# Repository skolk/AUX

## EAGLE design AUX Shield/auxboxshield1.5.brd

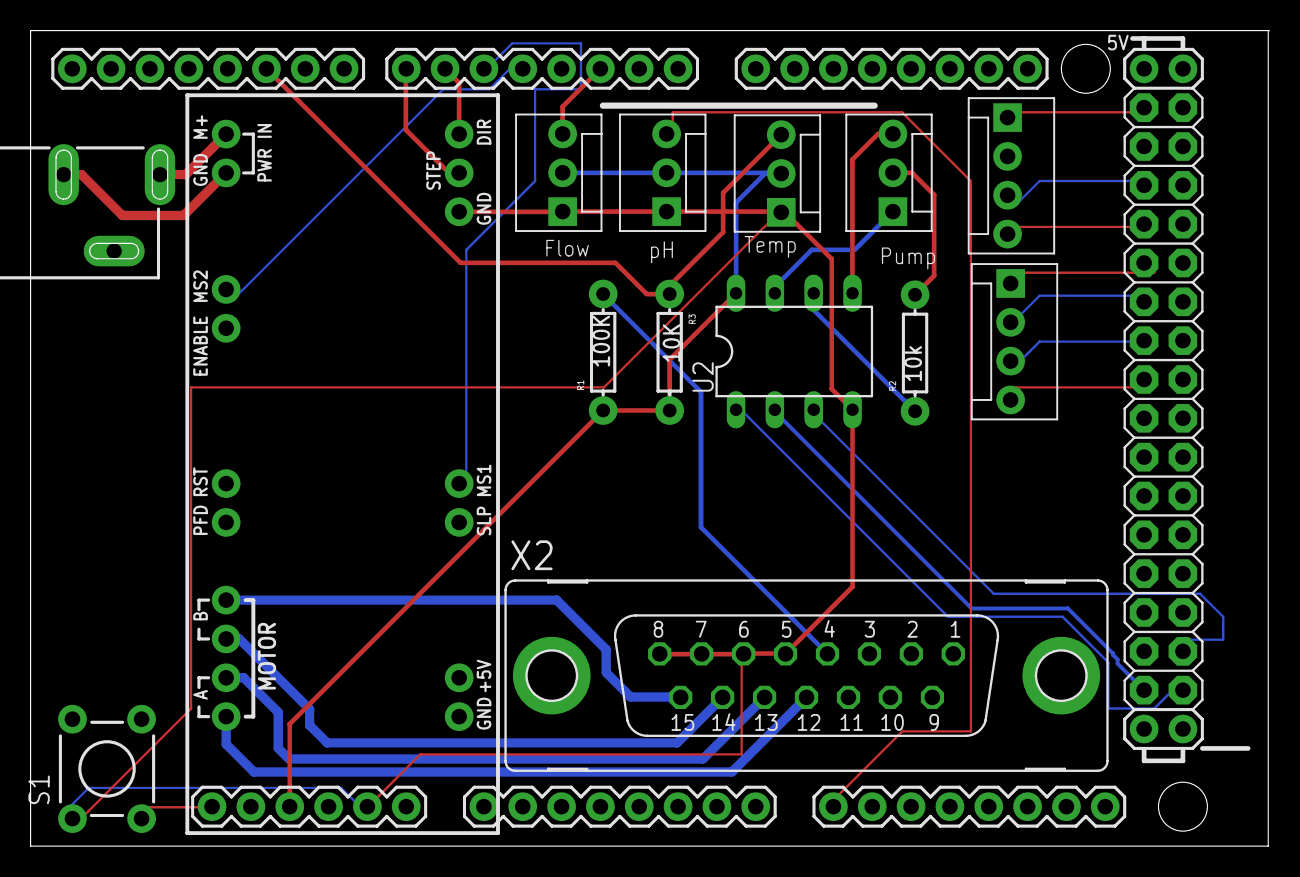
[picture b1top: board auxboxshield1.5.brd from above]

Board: 2 copper layers, 81.0 x 53.3 mm, 15 parts (0 on the bottom side), 34 nets.

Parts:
AMSHD1: ARDUINO_MEGA_SHIELD
EASYDRIVER_V44: EASYDRIVER_V44
JP1, JP2, JP3, JP11: MOLEX-1X3
JP4, JP5: MOLEX-1X4
R1: 100K; AXIAL-0.3
R2: 10k; AXIAL-0.3
R3: 10K; AXIAL-0.3
S1: SWITCH-MOMENTARY-2PTH_EZ; TACTILE-PTH-EZ
U2: MCP41XXXDIL; DIL-08
X1: SCD-014-A
X2: F15VP

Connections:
+5V: AMSHD1.5V@0, JP1.2, JP2.2, JP11.2, R1.P$1, R3.P$2, U2.8, X2.1, X2.2
GND-ISO: AMSHD1.GND@1, EASYDRIVER_V44.GND2, JP1.1, JP2.1, JP11.1, S1.1, U2.4, X2.5, X2.6, X2.7, X2.8
unnamed: EASYDRIVER_V44.M+, X1.1
unnamed: AMSHD1.36, JP5.4
unnamed: AMSHD1.38, X2.10
unnamed: R1.P$2, X2.3, X2.4
unnamed: AMSHD1.22, JP4.1
unnamed: EASYDRIVER_V44.GND1, X1.2
unnamed: EASYDRIVER_V44.A1, X2.12
unnamed: AMSHD1.24, JP4.2
unnamed: AMSHD1.RESET, S1.3
unnamed: AMSHD1.26, JP4.3
unnamed: EASYDRIVER_V44.A2, X2.13
unnamed: AMSHD1.53, U2.1
unnamed: AMSHD1.5, EASYDRIVER_V44.MS1
unnamed: AMSHD1.28, JP4.4
unnamed: AMSHD1.A8, JP11.3
unnamed: AMSHD1.4, EASYDRIVER_V44.MS2
unnamed: AMSHD1.52, U2.2
unnamed: AMSHD1.30, JP5.1
unnamed: AMSHD1.40, X2.9
unnamed: AMSHD1.51, U2.3
unnamed: JP3.3, U2.5
unnamed: AMSHD1.32, JP5.2
unnamed: AMSHD1.34, JP5.3
unnamed: R2.P$1, U2.6
unnamed: JP3.2, R2.P$2
unnamed: AMSHD1.10, JP2.3, R3.P$1
unnamed: EASYDRIVER_V44.B2, X2.14
unnamed: AMSHD1.2, JP1.3
unnamed: AMSHD1.6, EASYDRIVER_V44.DIR
unnamed: AMSHD1.7, EASYDRIVER_V44.STEP
unnamed: EASYDRIVER_V44.B1, X2.15
unnamed: JP3.1, U2.7

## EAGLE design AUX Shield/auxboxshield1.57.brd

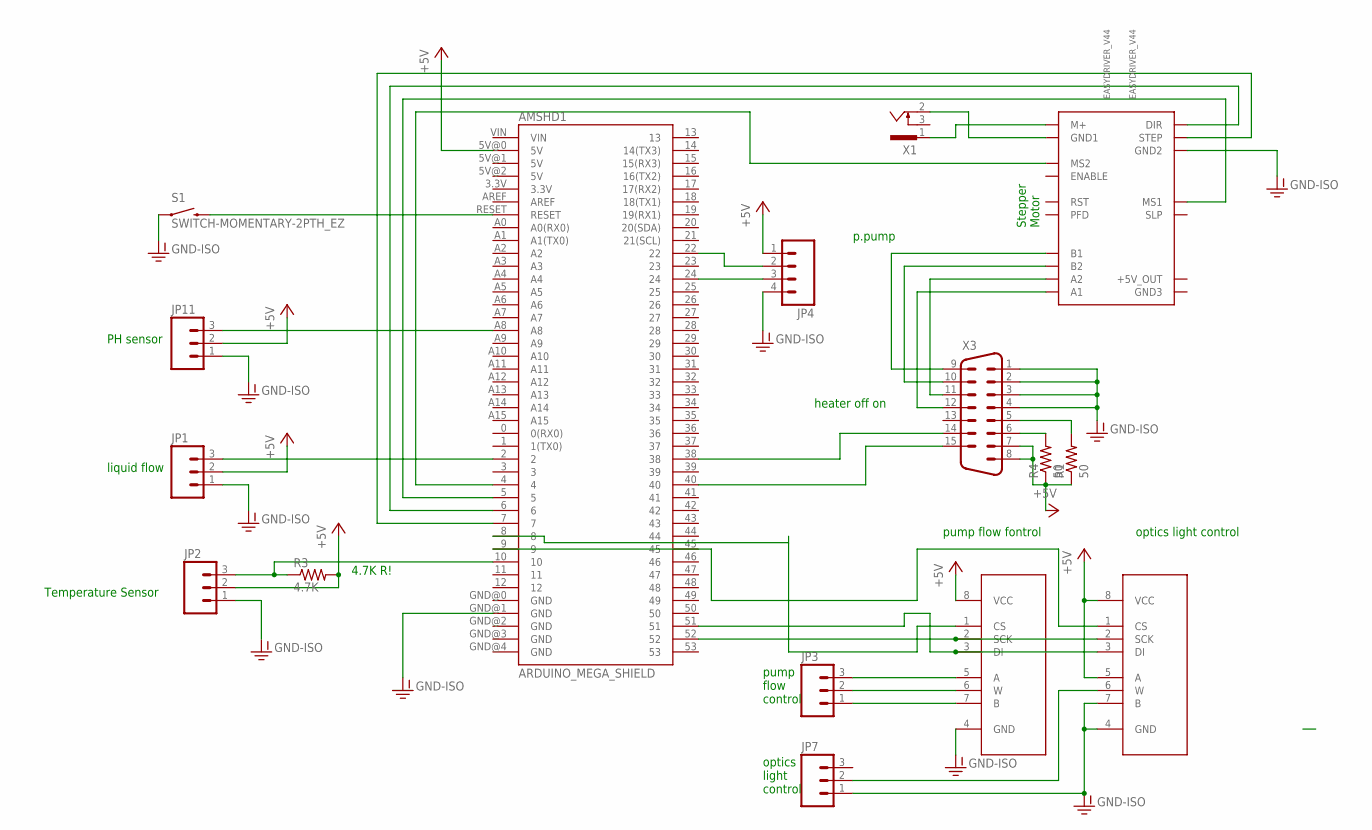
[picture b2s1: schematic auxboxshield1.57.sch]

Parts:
AMSHD1: ARDUINO_MEGA_SHIELD
EASYDRIVER_V44: EASYDRIVER_V44
JP1, JP2, JP3, JP7, JP11: M03POLAR; MOLEX-1X3
JP4: M04POLAR; MOLEX-1X4
R1, R4: 50; AXIAL-0.3
R3: 4.7K; AXIAL-0.3
S1: SWITCH-MOMENTARY-2PTH_EZ; TACTILE-PTH-EZ
U1, U2: MCP41XXXDIL; DIL-08
X1: SCD-014A; SCD-014-A
X3: M15V

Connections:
+5V: AMSHD1.5V@0 (5V), JP1.2, JP2.2, JP4.1, JP11.2, R1.P$1 (1), R3.P$2 (2), R4.P$1 (1), U1.5 (A), U1.8 (VCC), U2.8 (VCC), X3.7, X3.8
GND-ISO: AMSHD1.GND@1 (GND), EASYDRIVER_V44.GND2, JP1.1, JP2.1, JP4.4, JP7.1, JP11.1, S1.1, U1.4 (GND), U1.7 (B), U2.4 (GND), X3.1, X3.2, X3.3, X3.4
unnamed: EASYDRIVER_V44.M+, X1.1
unnamed: AMSHD1.38, X3.14
unnamed: R1.P$2 (2), X3.5
unnamed: EASYDRIVER_V44.GND1, X1.2
unnamed: EASYDRIVER_V44.A1, X3.12
unnamed: AMSHD1.RESET, S1.3 (2)
unnamed: AMSHD1.8, U2.1 (CS)
unnamed: EASYDRIVER_V44.A2, X3.11
unnamed: AMSHD1.5, EASYDRIVER_V44.MS1
unnamed: AMSHD1.9, U1.1 (CS)
unnamed: AMSHD1.A8, JP11.3
unnamed: AMSHD1.4, EASYDRIVER_V44.MS2
unnamed: AMSHD1.52, U1.2 (SCK), U2.2 (SCK)
unnamed: AMSHD1.24, JP4.3
unnamed: AMSHD1.40, X3.15
unnamed: AMSHD1.51, U1.3 (DI), U2.3 (DI)
unnamed: JP3.3, U2.5 (A)
unnamed: AMSHD1.22, JP4.2
unnamed: JP3.2, U2.6 (W)
unnamed: AMSHD1.10, JP2.3, R3.P$1 (1)
unnamed: EASYDRIVER_V44.B2, X3.10
unnamed: AMSHD1.2, JP1.3
unnamed: AMSHD1.6, EASYDRIVER_V44.DIR
unnamed: AMSHD1.7, EASYDRIVER_V44.STEP
unnamed: EASYDRIVER_V44.B1, X3.9
unnamed: JP3.1, U2.7 (B)
unnamed: R4.P$2 (2), X3.6
unnamed: JP7.2, U1.6 (W)

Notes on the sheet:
Stepper Motor
Temperature Sensor
liquid flow
PH sensor
4.7K R!
pump flow fontrol
optics light control
heater off on
p.pump
pump flow control
optics light control

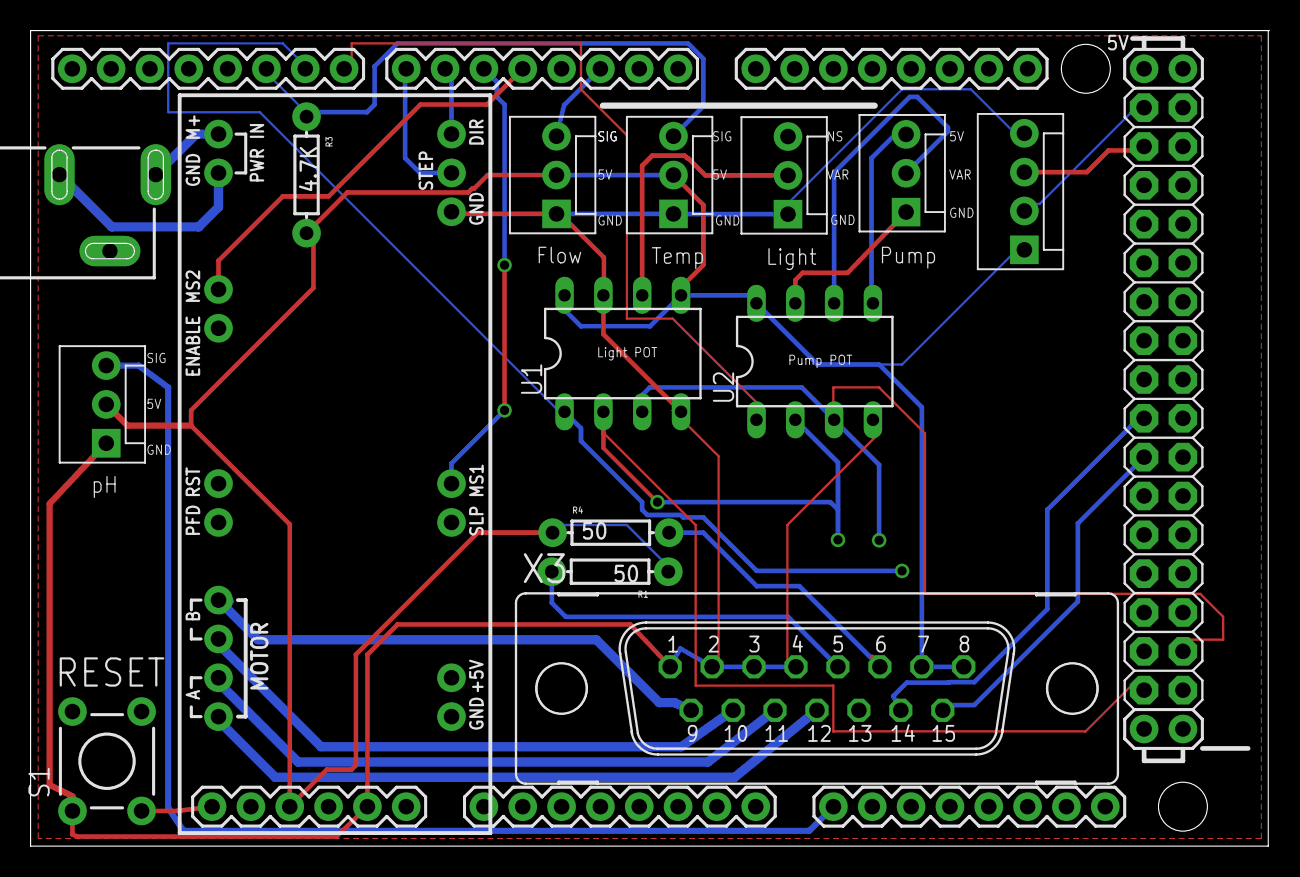
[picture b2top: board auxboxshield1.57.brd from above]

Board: 2 copper layers, 81.0 x 53.3 mm, 16 parts (0 on the bottom side), 30 nets.

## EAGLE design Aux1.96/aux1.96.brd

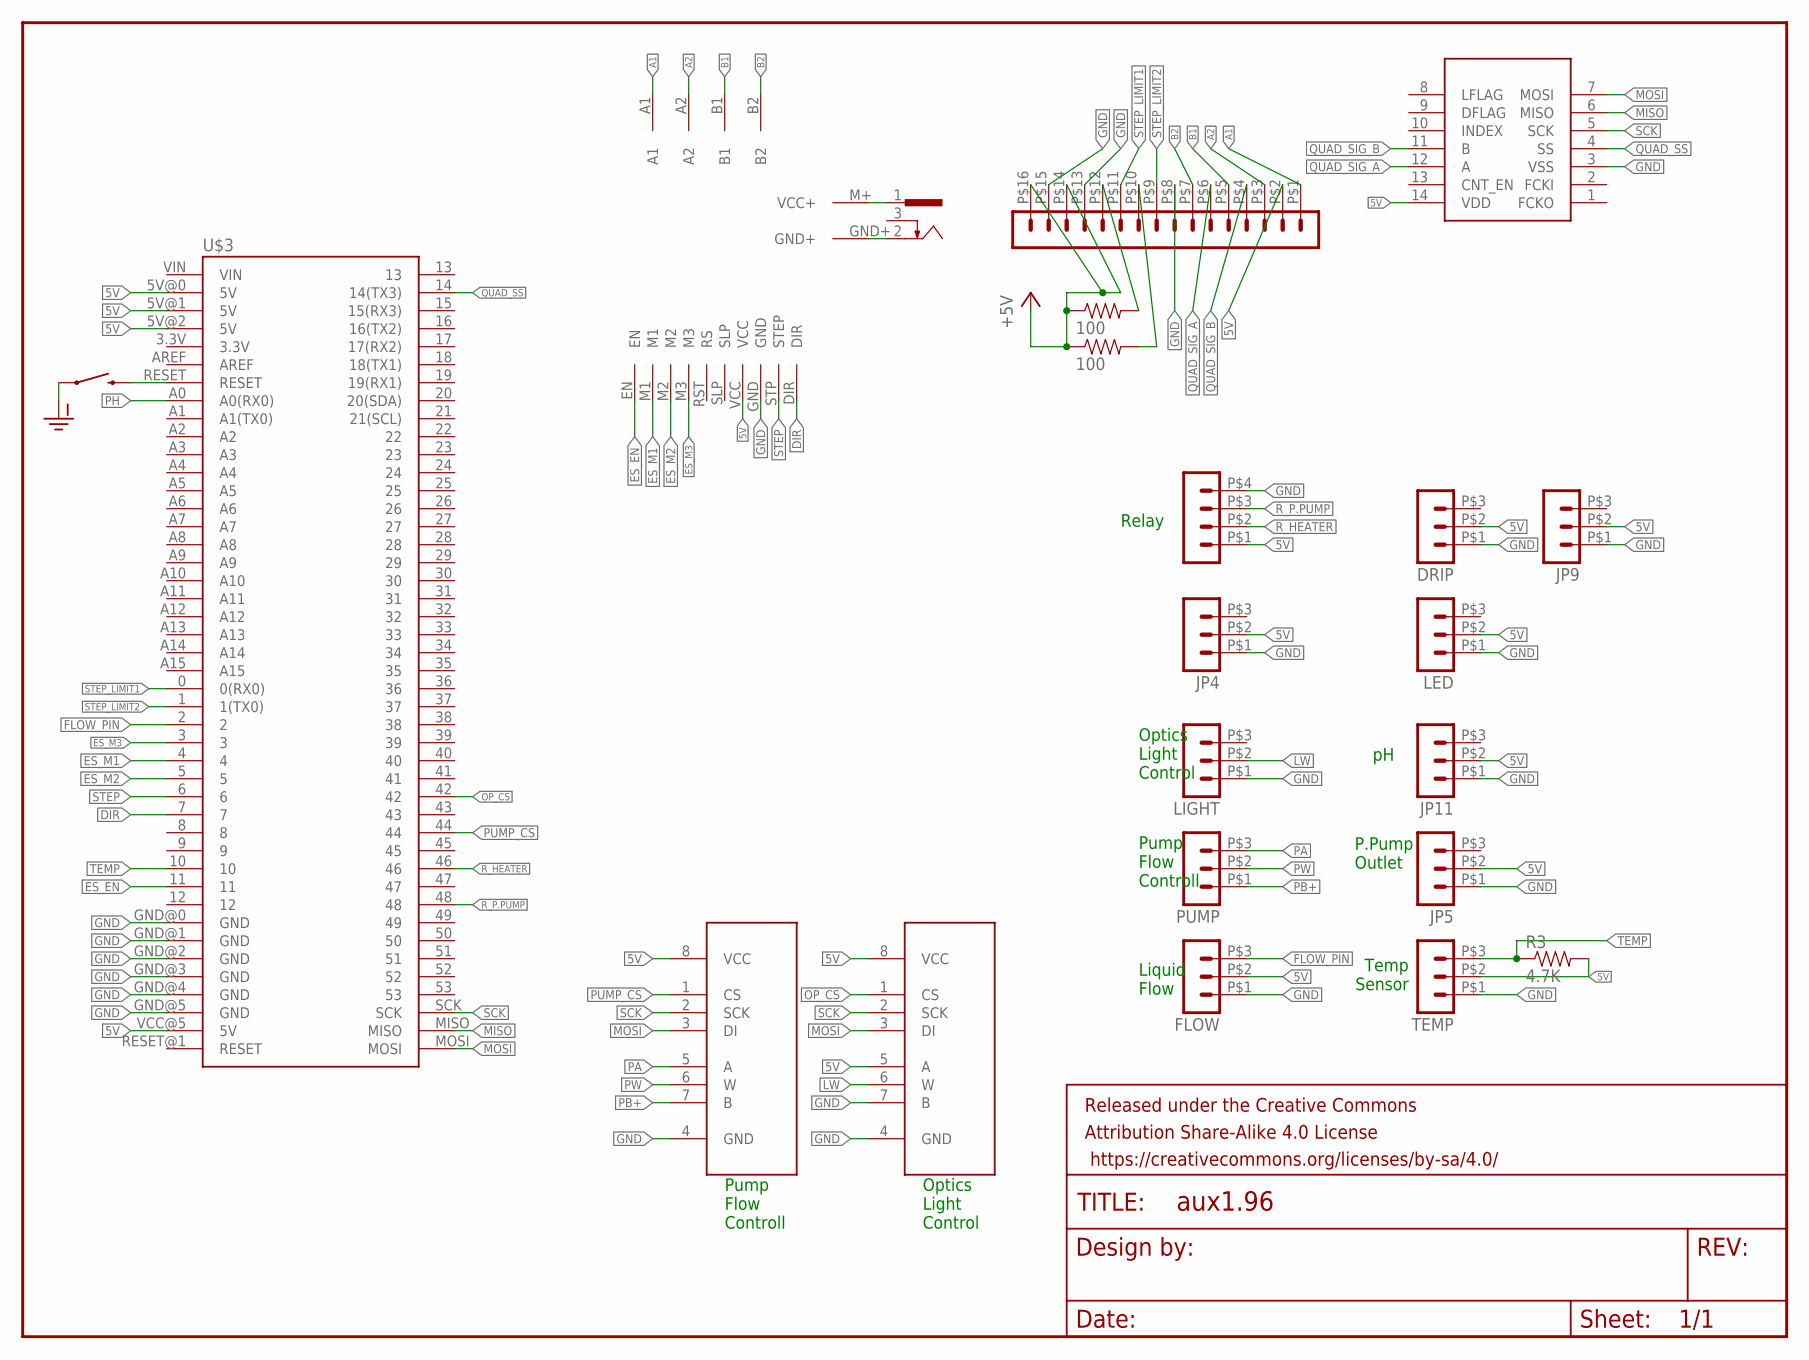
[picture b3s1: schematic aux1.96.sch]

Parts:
DRIP: HEADER_POS3_43650-0315; 43650-0315
FLOW: HEADER_POS3_43650-0315; 43650-0315
FRAME1: FRAME-LETTER; CREATIVE_COMMONS
JP4, JP5, JP9, JP11: HEADER_POS3_43650-0315; 43650-0315
LED: HEADER_POS3_43650-0315; 43650-0315
LIGHT: HEADER_POS3_43650-0315; 43650-0315
PUMP: HEADER_POS3_43650-0315; 43650-0315
PUMPDIGIPOT: MCP41XXXDIL; DIL-08
R1, R4: 100; AXIAL-0.3
R3: 4.7K; AXIAL-0.3
RELAY: HEADER_POS4_44914-0401; 44914-0401
S1: SWITCH-MOMENTARY-2PTH_EZ; TACTILE-PTH-EZ
TEMP: HEADER_POS3_43650-0315; 43650-0315
U1: MCP41XXXDIL; DIL-08
U$1: HEADER_POS16_43045-1612; 43045-1612
U$2: LS7366R; SO014
U$3: ARDUINO-MEGA-V2; ARDUINO_MEGA-PRO-5V
U$4: BIG_EASY_DRIVER; BIG_EASY_DRIVER_PACK
X1: SCD-014A; SCD-014-A

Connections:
5V: DRIP.P$2 (2), FLOW.P$2 (2), JP4.P$2 (2), JP5.P$2 (2), JP9.P$2 (2), JP11.P$2 (2), LED.P$2 (2), PUMPDIGIPOT.8 (VCC), R1.P$1 (1), R3.P$2 (2), R4.P$1 (1), RELAY.P$1 (1), TEMP.P$2 (2), U1.5 (A), U1.8 (VCC), U$1.P$2 (2), U$1.P$14 (14), U$1.P$16 (16), U$2.14 (VDD), U$3.5V@0 (5V), U$3.5V@1 (5V), U$3.5V@2 (5V), U$3.VCC@5 (5V), U$4.VCC
A1: U$1.P$1 (1), U$4.A1
A2: U$1.P$3 (3), U$4.A2
B1: U$1.P$5 (5), U$4.B1
B2: U$1.P$7 (7), U$4.B2
DIR: U$3.7, U$4.DIR
ES_EN: U$3.11, U$4.EN
ES_M1: U$3.4, U$4.M1
ES_M2: U$3.5, U$4.M2
ES_M3: U$3.3, U$4.M3
FLOW_PIN: FLOW.P$3 (3), U$3.2
GND: DRIP.P$1 (1), FLOW.P$1 (1), JP4.P$1 (1), JP5.P$1 (1), JP9.P$1 (1), JP11.P$1 (1), LED.P$1 (1), LIGHT.P$1 (1), PUMPDIGIPOT.4 (GND), RELAY.P$4 (4), S1.1, TEMP.P$1 (1), U1.4 (GND), U1.7 (B), U$1.P$8 (8), U$1.P$13 (13), U$1.P$15 (15), U$2.3 (VSS), U$3.GND@0 (GND), U$3.GND@1 (GND), U$3.GND@2 (GND), U$3.GND@3 (GND), U$3.GND@4 (GND), U$3.GND@5 (GND), U$4.GND
LW: LIGHT.P$2 (2), U1.6 (W)
MISO: U$2.6 (MISO), U$3.MISO
MOSI: PUMPDIGIPOT.3 (DI), U1.3 (DI), U$2.7 (MOSI), U$3.MOSI
unnamed: U$4.M+ (VCC+), X1.1
unnamed: U$4.GND+, X1.2
unnamed: R1.P$2 (2), U$1.P$10 (10)
unnamed: S1.3 (2), U$3.RESET
unnamed: R4.P$2 (2), U$1.P$12 (12)
OP_CS: U1.1 (CS), U$3.42
PA: PUMP.P$3 (3), PUMPDIGIPOT.5 (A)
PB+: PUMP.P$1 (1), PUMPDIGIPOT.7 (B)
PH: U$3.A0 (A0(RX0))
PUMP_CS: PUMPDIGIPOT.1 (CS), U$3.44
PW: PUMP.P$2 (2), PUMPDIGIPOT.6 (W)
QUAD_SIG_A: U$1.P$6 (6), U$2.12 (A)
QUAD_SIG_B: U$1.P$4 (4), U$2.11 (B)
QUAD_SS: U$2.4 (SS), U$3.14 (14(TX3))
R_HEATER: RELAY.P$2 (2), U$3.46
R_P.PUMP: RELAY.P$3 (3), U$3.48
SCK: PUMPDIGIPOT.2 (SCK), U1.2 (SCK), U$2.5 (SCK), U$3.SCK
STEP: U$3.6, U$4.STP (STEP)
STEP_LIMIT1: U$1.P$11 (11), U$3.0 (0(RX0))
STEP_LIMIT2: U$1.P$9 (9), U$3.1 (1(TX0))
TEMP: R3.P$1 (1), TEMP.P$3 (3), U$3.10

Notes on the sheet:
Temp Sensor
Liquid Flow
Pump Flow Controll
Optics Light Control
Optics Light Control
P.Pump Outlet
Relay

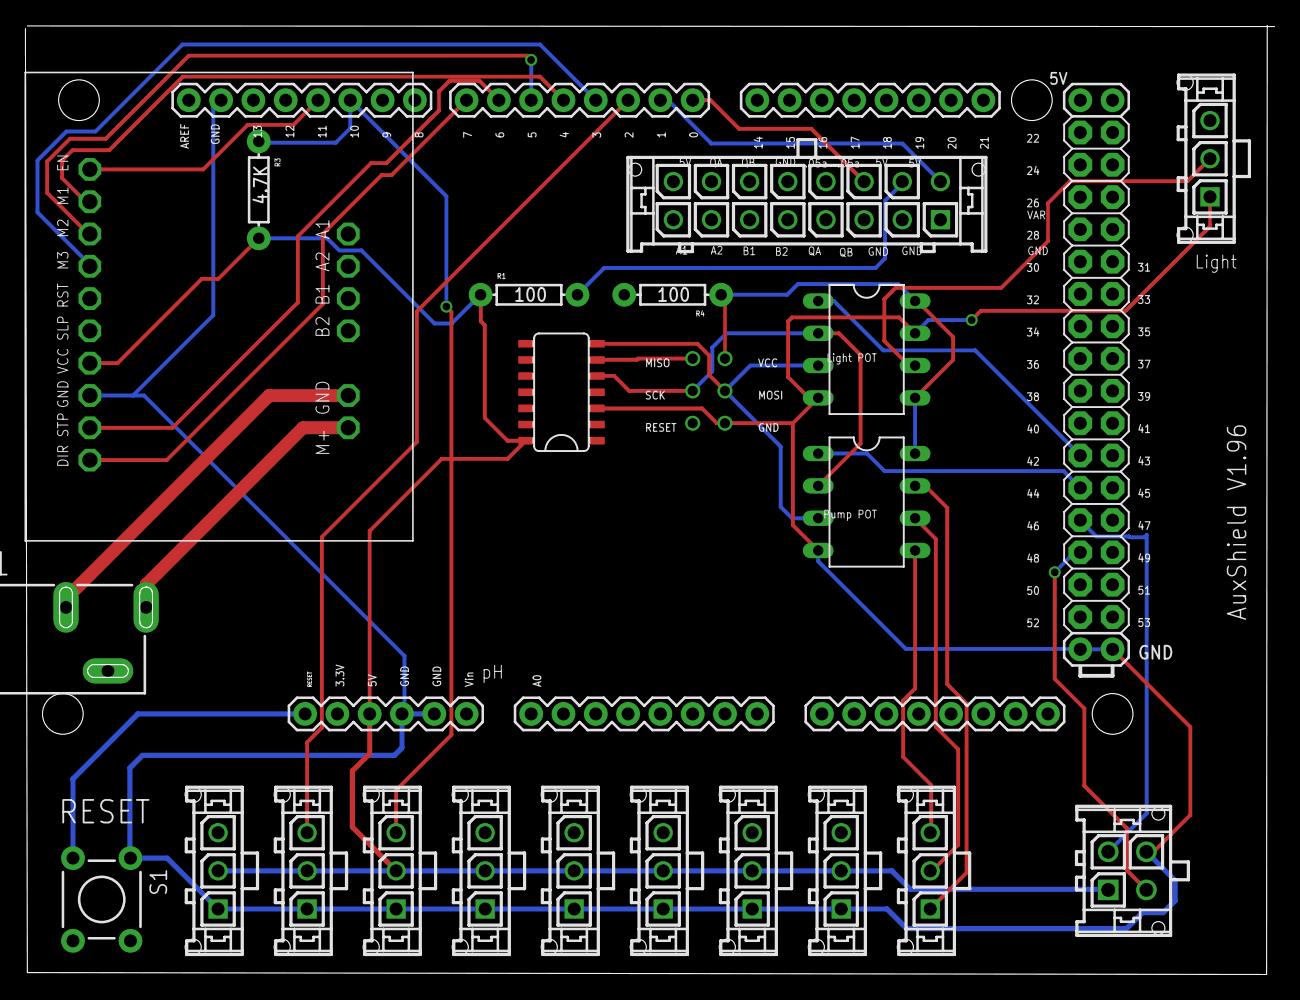
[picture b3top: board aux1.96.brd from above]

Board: 2 copper layers, 98.2 x 74.6 mm, 23 parts (0 on the bottom side), 35 nets.

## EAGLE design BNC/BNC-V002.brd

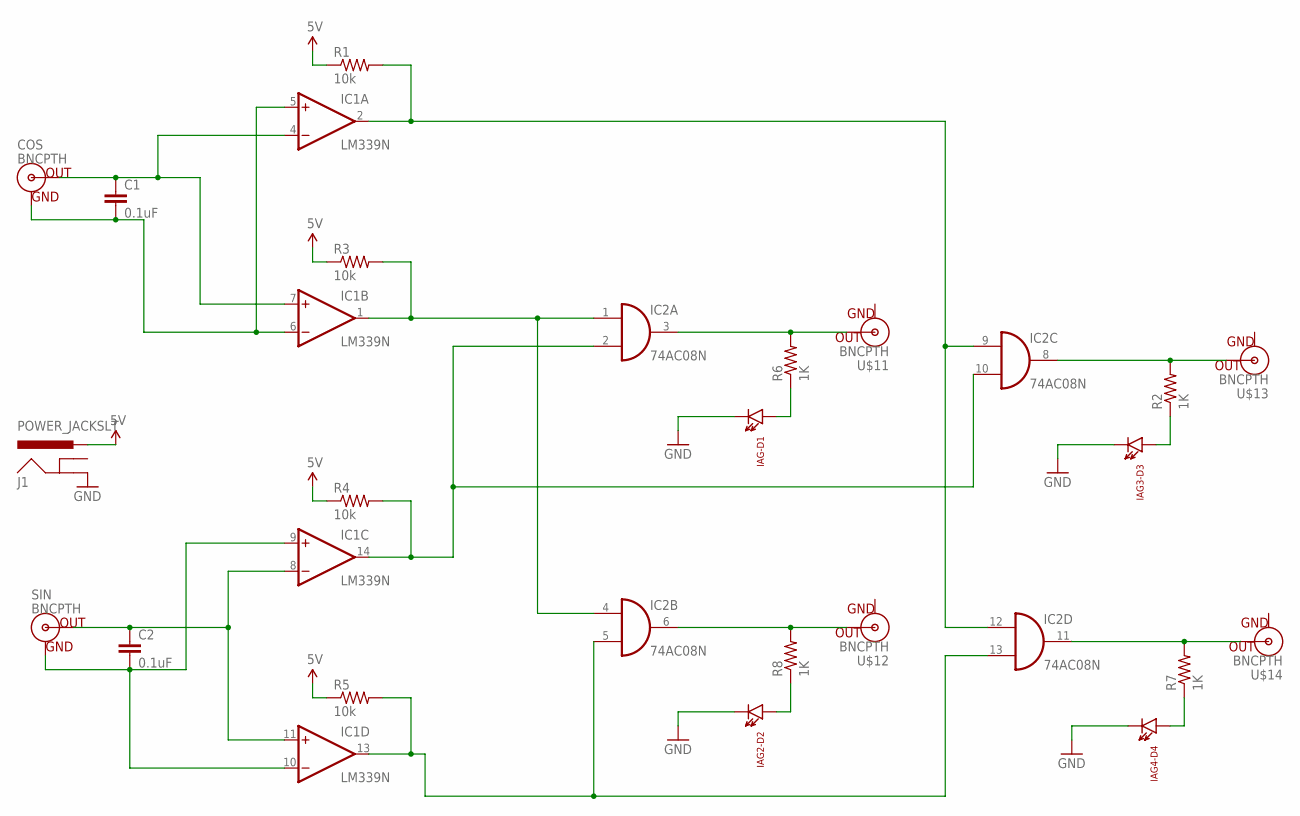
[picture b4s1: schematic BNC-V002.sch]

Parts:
C1, C2: 0.1uF; 0603-CAP
COS: BNCPTH; BNC
IAG2-D2, IAG3-D3, IAG4-D4: LTE-302
IAG-D1: LTE-302
IC1: LM339N; DIL14
IC2: 74AC08N; DIL14
J1: POWER_JACKSLT; POWER_JACK_SLOT
R1, R3, R4, R5: 10k; AXIAL-0.3
R2, R6, R7, R8: 1K; AXIAL-0.3
SIN: BNCPTH; BNC
U$11, U$12, U$13, U$14: BNCPTH; BNC

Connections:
5V: J1.PWR, R1.P$1 (1), R3.P$1 (1), R4.P$1 (1), R5.P$1 (1)
GND: IAG2-D2.C, IAG3-D3.C, IAG4-D4.C, IAG-D1.C, IC1.12 (GND), IC2.7 (GND), J1.GND@2 (GND)
unnamed: IC1.2 (OUT), IC2.9 (I0), IC2.12 (I0), R1.P$2 (2)
unnamed: IC2.11 (O), R7.P$2 (2), U$14.S (OUT)
unnamed: IAG4-D4.A, R7.P$1 (1)
unnamed: IC1.1 (OUT), IC2.1 (I0), IC2.4 (I0), R3.P$2 (2)
unnamed: IC1.14 (OUT), IC2.2 (I1), IC2.10 (I1), R4.P$2 (2)
unnamed: IC1.13 (OUT), IC2.5 (I1), IC2.13 (I1), R5.P$2 (2)
unnamed: C1.2, COS.GND, IC1.5 (+IN), IC1.6 (-IN)
unnamed: C1.1, COS.S (OUT), IC1.4 (-IN), IC1.7 (+IN)
unnamed: C2.1, IC1.8 (-IN), IC1.11 (+IN), SIN.S (OUT)
unnamed: C2.2, IC1.9 (+IN), IC1.10 (-IN), SIN.GND
unnamed: IC2.8 (O), R2.P$2 (2), U$13.S (OUT)
unnamed: IAG3-D3.A, R2.P$1 (1)
unnamed: IC2.6 (O), R8.P$2 (2), U$12.S (OUT)
unnamed: IAG2-D2.A, R8.P$1 (1)
unnamed: IC2.3 (O), R6.P$2 (2), U$11.S (OUT)
unnamed: IAG-D1.A, R6.P$1 (1)
V+: IC1.3 (V+)
VCC: IC2.14 (VCC)

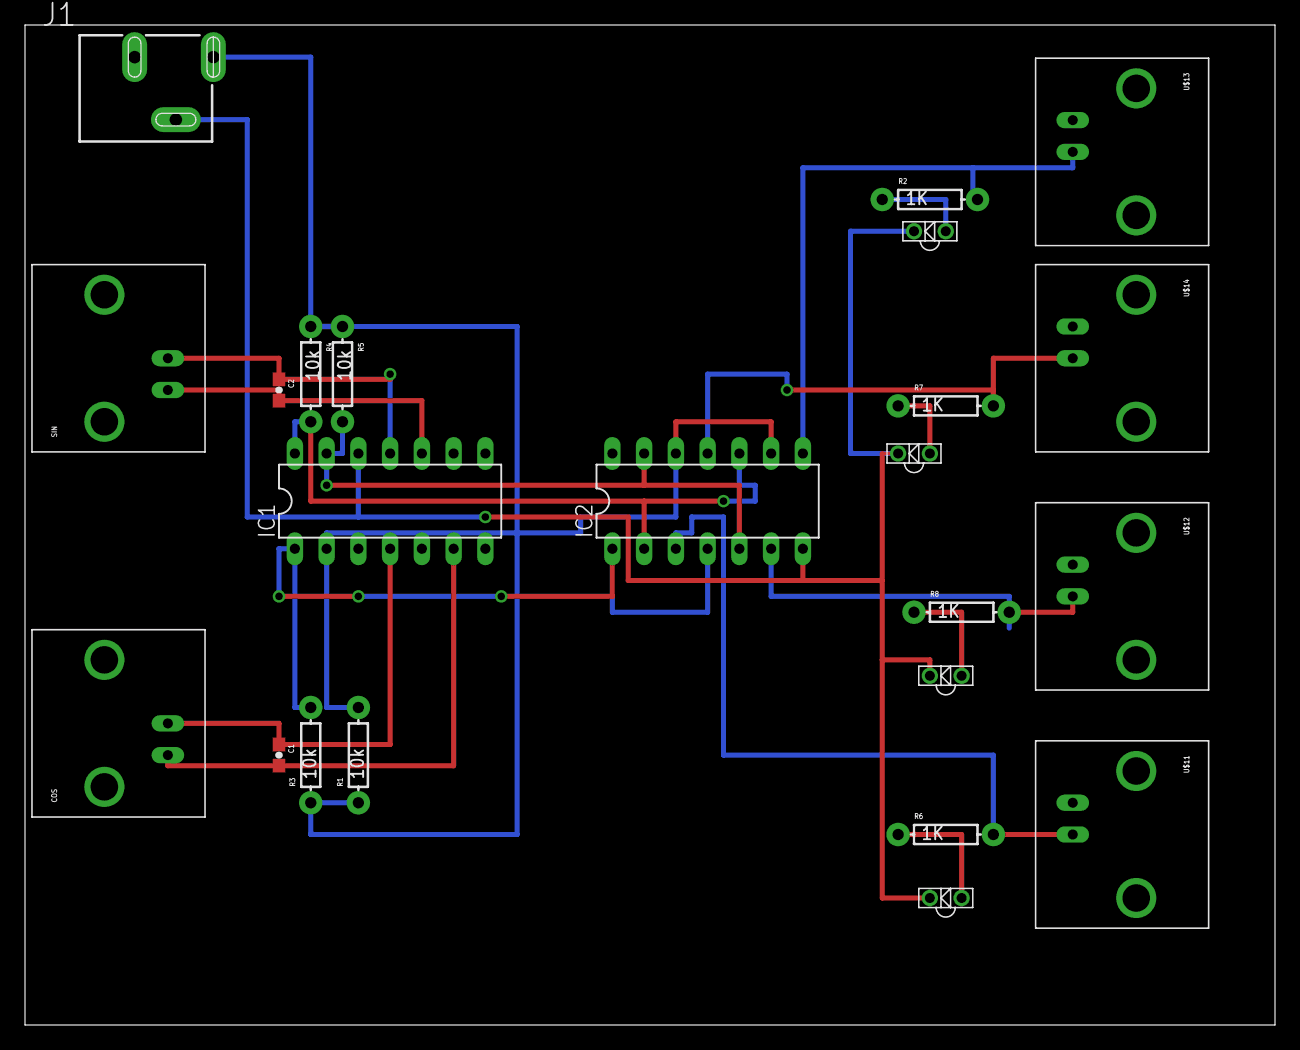
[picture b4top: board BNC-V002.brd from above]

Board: 2 copper layers, 100.0 x 80.0 mm, 23 parts (0 on the bottom side), 18 nets.

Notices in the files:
parts and their libraries:
SparkFun-Connectors: Licensing: Creative Commons ShareAlike 4.0 International - https://creativecommons.org/licenses/by-sa/4.0
SparkFun-Aesthetics: Released under the Creative Commons Attribution Share-Alike 4.0 License
SparkFun-Aesthetics: https://creativecommons.org/licenses/by-sa/4.0
